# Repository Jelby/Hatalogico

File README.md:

##Hatalogico
Libraries for the Hatalogico Raspberry Pi Hat

###Cloning This Repo
When cloning, it is crucial that you use the --recursive switch in order to fetch the Adafruit submodules.

All the python files required to drive the I2C chips on the Hatalogico were written and are maintained by [Adafruit Industries](https://www.adafruit.com/). I have simply included them as submodules and written a few examples using them.

Before using these files, you need to setup your Pi for GPIO and I2C (note the Pi 2 has a slightly different method for the latter).

[Setting up the I2C](https://learn.adafruit.com/adafruits-raspberry-pi-lesson-4-gpio-setup/configuring-i2c)

[Setting up the GPIO](https://learn.adafruit.com/adafruits-raspberry-pi-lesson-4-gpio-setup/configuring-gpio)

##Installing
The RPi2 is slightly different but I recommend you 'apt-get' the following packages on both platforms:

**sudo apt-get update -y**  
**sudo apt-get install -y python-dev python-rpi.gpio python-smbus**  
**sudo apt-get install -y i2c-tools libi2c-dev**

You can copy and paste all 3 lines into your terminal and they will run one after the other (synchronously).

You will need to add the I2C tools to both versions:  
**sudo nano /etc/modules**

Scroll to the bottom and add:  
**i2c-dev**

####For RPi B+ and older only:
Also add a new line underneath 'i2c-dev':  
**i2c-bcm2708**

Crtl-X to close, pressing Y to save the changes (overwrite with the same name by pressing enter)

####For the RPi B+ or older you will need to update the blacklist file:  
**sudo nano /etc/modprobe.d/raspi-blacklist.conf**

Update it to read:  
\#blacklist spi-bcm2708  
\#blacklist i2c-bcm2708

After all of this, it's wise to do a little housekeeping (perhaps even removing some unused libraries):  
**sudo apt-get -y purge wolfram-engine**  
**sudo apt-get -y autoremove**  
**sudo apt-get -y clean**  
**sudo apt-get -y update**  
**sudo apt-get -y dist-upgrade**  

#I2C Addresses
(on the prototype model)

1. 16 Channel PWM: **0x70**
2. 4 Channel ADC #1: **0x49**
3. 4 Channel ADC #2: **0x48**
4. Single Channel DAC #1: **0x60**
5. Single Channel DAC #2: **0x61**

###Big thanks to Adafruit without whom the Hatalogico would just be a mug coaster.

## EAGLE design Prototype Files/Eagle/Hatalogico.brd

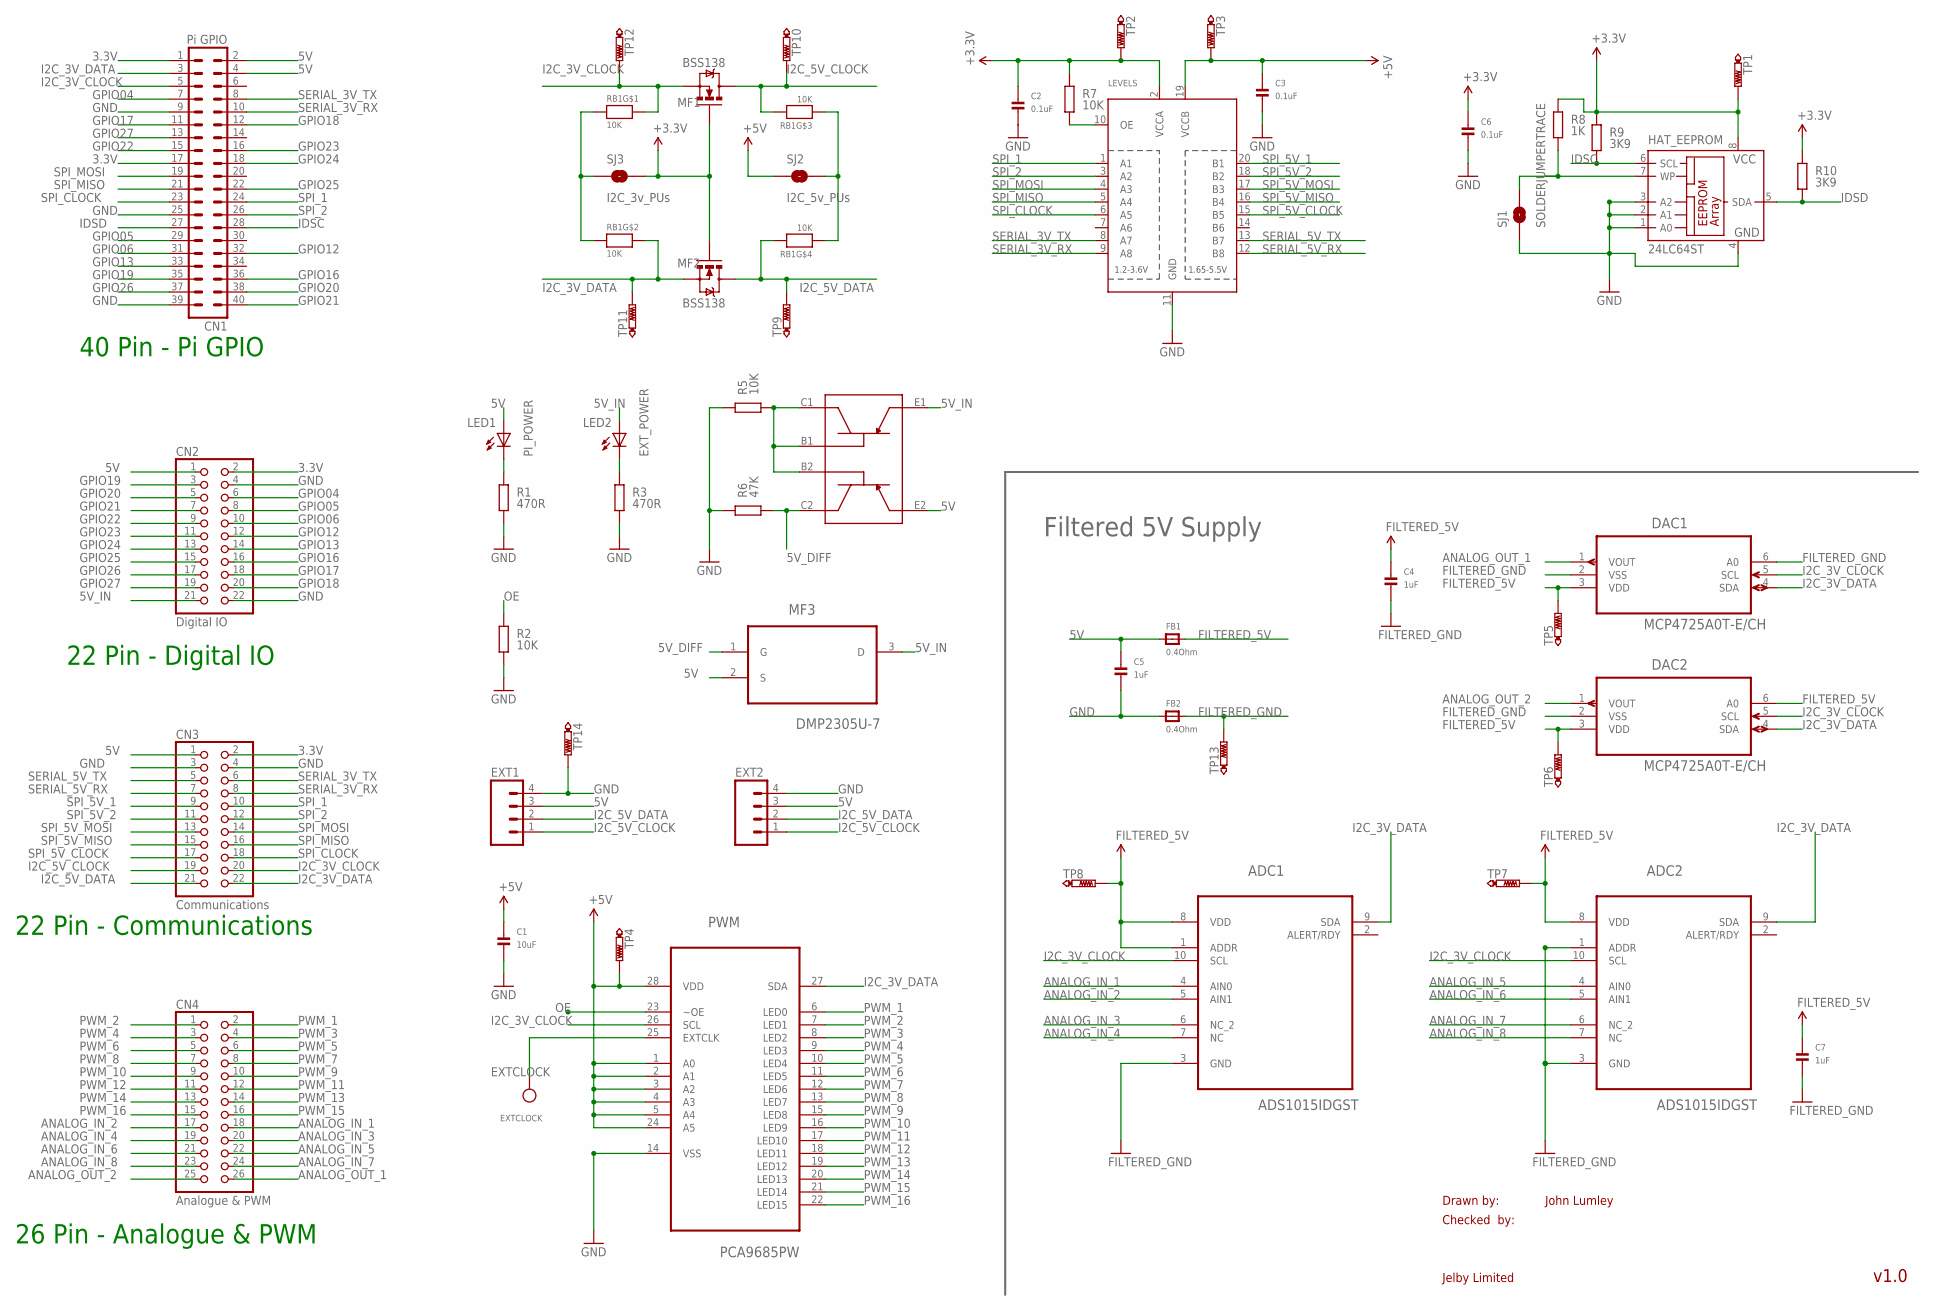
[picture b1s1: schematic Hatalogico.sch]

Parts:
ADC1, ADC2: ADS1015IDGST; SOP50P490X110-10N
C1: 10uF; 0603
C2, C3, C6: 0.1uF; 0603
C4, C5, C7: 1uF; 0603
CN1: Pi GPIO; PIN_20X2
CN2: Digital IO; 2X11
CN3: Communications; 2X11
CN4: Analogue & PWM; 2X13
DAC1, DAC2: MCP4725A0T-E/CH; SOT95P270X145-6N
EXT1, EXT2: 1X04_HEADER"; 1X04_HEADER
EXTCLOCK: TESTPOINT0.1"; 1X01_ROUND
FB1, FB2: 0.4Ohm; 0805
HAT_EEPROM: 24LC64ST; TSSOP8
LED1: PI_POWER; CHIPLED_1206
LED2: EXT_POWER; CHIPLED_1206
LEVELS: TXB0108PWR; TSSOP20
MF1, MF2: BSS138; SOT23-3
MF3: DMP2305U-7; SOT103P240X110-3N
PWM: PCA9685PW; SOP65P640X110-28N
R1, R3: 470R; M0805; TOLERANCE 5%
R2, R5, R7: 10K; M0805; TOLERANCE 5%
R6: 47K; M0805; TOLERANCE 5%
R8: 1K; M0805; TOLERANCE 5%
R9, R10: 3K9; M0805; TOLERANCE 5%
RB1: 10K; RESPACK_4X0603
SJ1: SOLDERJUMPERTRACE; SJ_2S-TRACE
SJ2: I2C_5v_PUs; PAD-JUMPER-2-NO_YES_SILK
SJ3: I2C_3v_PUs; PAD-JUMPER-2-NO_YES_SILK
T1: DMMT5401
TP1, TP2, TP3, TP4, TP5, TP6, TP7, TP8, TP9, TP10, TP11, TP12, TP13, TP14: PTR1TP20SQ; TP20SQ

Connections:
3.3V: C2.1, C6.1, CN1.1, CN1.17, CN2.2, CN3.2, HAT_EEPROM.8 (VCC), LEVELS.2 (VCCA), MF1.1 (G), MF2.1 (G), R7.2, R8.2, R9.2, R10.2, SJ3.2, TP1.TP, TP2.TP
5V: C1.1, C3.1, C5.1, CN1.2, CN1.4, CN2.1, CN3.1, EXT1.3, EXT2.3, FB1.1, LED1.A, LEVELS.19 (VCCB), MF3.2 (S), PWM.1 (A0), PWM.2 (A1), PWM.3 (A2), PWM.4 (A3), PWM.5 (A4), PWM.24 (A5), PWM.28 (VDD), SJ2.1, T1.E2, TP3.TP, TP4.TP
5V_DIFF: MF3.1 (G), R6.1, T1.C2
5V_IN: CN2.21, LED2.A, MF3.3 (D), T1.E1
ANALOG_IN_1: ADC1.4 (AIN0), CN4.18
ANALOG_IN_2: ADC1.5 (AIN1), CN4.17
ANALOG_IN_3: ADC1.6 (NC_2), CN4.20
ANALOG_IN_4: ADC1.7 (NC), CN4.19
ANALOG_IN_5: ADC2.4 (AIN0), CN4.22
ANALOG_IN_6: ADC2.5 (AIN1), CN4.21
ANALOG_IN_7: ADC2.6 (NC_2), CN4.24
ANALOG_IN_8: ADC2.7 (NC), CN4.23
ANALOG_OUT_1: CN4.26, DAC1.1 (VOUT)
ANALOG_OUT_2: CN4.25, DAC2.1 (VOUT)
EXTCLOCK: EXTCLOCK.1, PWM.25 (EXTCLK)
FILTERED_5V: ADC1.1 (ADDR), ADC1.8 (VDD), ADC2.8 (VDD), C4.1, C7.1, DAC1.3 (VDD), DAC2.3 (VDD), DAC2.6 (A0), FB1.2, TP5.TP, TP6.TP, TP7.TP, TP8.TP
FILTERED_GND: ADC1.3 (GND), ADC2.1 (ADDR), ADC2.3 (GND), C4.2, C7.2, DAC1.2 (VSS), DAC1.6 (A0), DAC2.2 (VSS), FB2.2, TP13.TP
GND: C1.2, C2.2, C3.2, C5.2, C6.2, CN1.9, CN1.25, CN1.39, CN2.4, CN2.22, CN3.3, CN3.4, EXT1.4, EXT2.4, FB2.1, HAT_EEPROM.1 (A0), HAT_EEPROM.2 (A1), HAT_EEPROM.3 (A2), HAT_EEPROM.4 (GND), LEVELS.11 (GND), PWM.14 (VSS), R1.1, R2.1, R3.1, R5.2, R6.2, SJ1.1, TP14.TP
GPIO04: CN1.7, CN2.6
GPIO05: CN1.29, CN2.8
GPIO06: CN1.31, CN2.10
GPIO12: CN1.32, CN2.12
GPIO13: CN1.33, CN2.14
GPIO16: CN1.36, CN2.16
GPIO17: CN1.11, CN2.18
GPIO18: CN1.12, CN2.20
GPIO19: CN1.35, CN2.3
GPIO20: CN1.38, CN2.5
GPIO21: CN1.40, CN2.7
GPIO22: CN1.15, CN2.9
GPIO23: CN1.16, CN2.11
GPIO24: CN1.18, CN2.13
GPIO25: CN1.22, CN2.15
GPIO26: CN1.37, CN2.17
GPIO27: CN1.13, CN2.19
I2C_3V_CLOCK: ADC1.10 (SCL), ADC2.10 (SCL), CN1.5, CN3.20, DAC1.5 (SCL), DAC2.5 (SCL), MF1.2 (S), PWM.26 (SCL), RB1.8 (2), TP12.TP
I2C_3V_DATA: ADC1.9 (SDA), ADC2.9 (SDA), CN1.3, CN3.22, DAC1.4 (SDA), DAC2.4 (SDA), MF2.2 (S), PWM.27 (SDA), RB1.7 (2), TP11.TP
I2C_5V_CLOCK: CN3.19, EXT1.1, EXT2.1, MF1.3 (D), RB1.6 (2), TP10.TP
I2C_5V_DATA: CN3.21, EXT1.2, EXT2.2, MF2.3 (D), RB1.5 (2), TP9.TP
IDSC: CN1.28, HAT_EEPROM.6 (SCL), R9.1
IDSD: CN1.27, HAT_EEPROM.5 (SDA), R10.1
LEDOUT: LED1.C, R1.2
LEDOUT1: LED2.C, R3.2
unnamed: R5.1, T1.B1, T1.B2, T1.C1
unnamed: RB1.1, RB1.2 (1), SJ3.1
unnamed: RB1.3 (1), RB1.4 (1), SJ2.2
unnamed: LEVELS.10 (OE), R7.1
OE: PWM.23 (~OE), R2.2
PWM_1: CN4.2, PWM.6 (LED0)
PWM_2: CN4.1, PWM.7 (LED1)
PWM_3: CN4.4, PWM.8 (LED2)
PWM_4: CN4.3, PWM.9 (LED3)
PWM_5: CN4.6, PWM.10 (LED4)
PWM_6: CN4.5, PWM.11 (LED5)
PWM_7: CN4.8, PWM.12 (LED6)
PWM_8: CN4.7, PWM.13 (LED7)
PWM_9: CN4.10, PWM.15 (LED8)
PWM_10: CN4.9, PWM.16 (LED9)
PWM_11: CN4.12, PWM.17 (LED10)
PWM_12: CN4.11, PWM.18 (LED11)
PWM_13: CN4.14, PWM.19 (LED12)
PWM_14: CN4.13, PWM.20 (LED13)
PWM_15: CN4.16, PWM.21 (LED14)
PWM_16: CN4.15, PWM.22 (LED15)
SERIAL_3V_RX: CN1.10, CN3.8, LEVELS.9 (A8)
SERIAL_3V_TX: CN1.8, CN3.6, LEVELS.8 (A7)
SERIAL_5V_RX: CN3.7, LEVELS.12 (B8)
SERIAL_5V_TX: CN3.5, LEVELS.13 (B7)
SPI_1: CN1.24, CN3.10, LEVELS.1 (A1)
SPI_2: CN1.26, CN3.12, LEVELS.3 (A2)
SPI_5V_1: CN3.9, LEVELS.20 (B1)
SPI_5V_2: CN3.11, LEVELS.18 (B2)
SPI_5V_CLOCK: CN3.17, LEVELS.15 (B5)
SPI_5V_MISO: CN3.15, LEVELS.16 (B4)
SPI_5V_MOSI: CN3.13, LEVELS.17 (B3)
SPI_CLOCK: CN1.23, CN3.18, LEVELS.6 (A5)
SPI_MISO: CN1.21, CN3.16, LEVELS.5 (A4)
SPI_MOSI: CN1.19, CN3.14, LEVELS.4 (A3)
WP: HAT_EEPROM.7 (WP), R8.1, SJ1.2

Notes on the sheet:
Drawn by:
Checked by:
Jelby Limited
John Lumley
v1.0
40 Pin - Pi GPIO
26 Pin - Analogue & PWM
22 Pin - Digital IO
22 Pin - Communications
Filtered 5V Supply

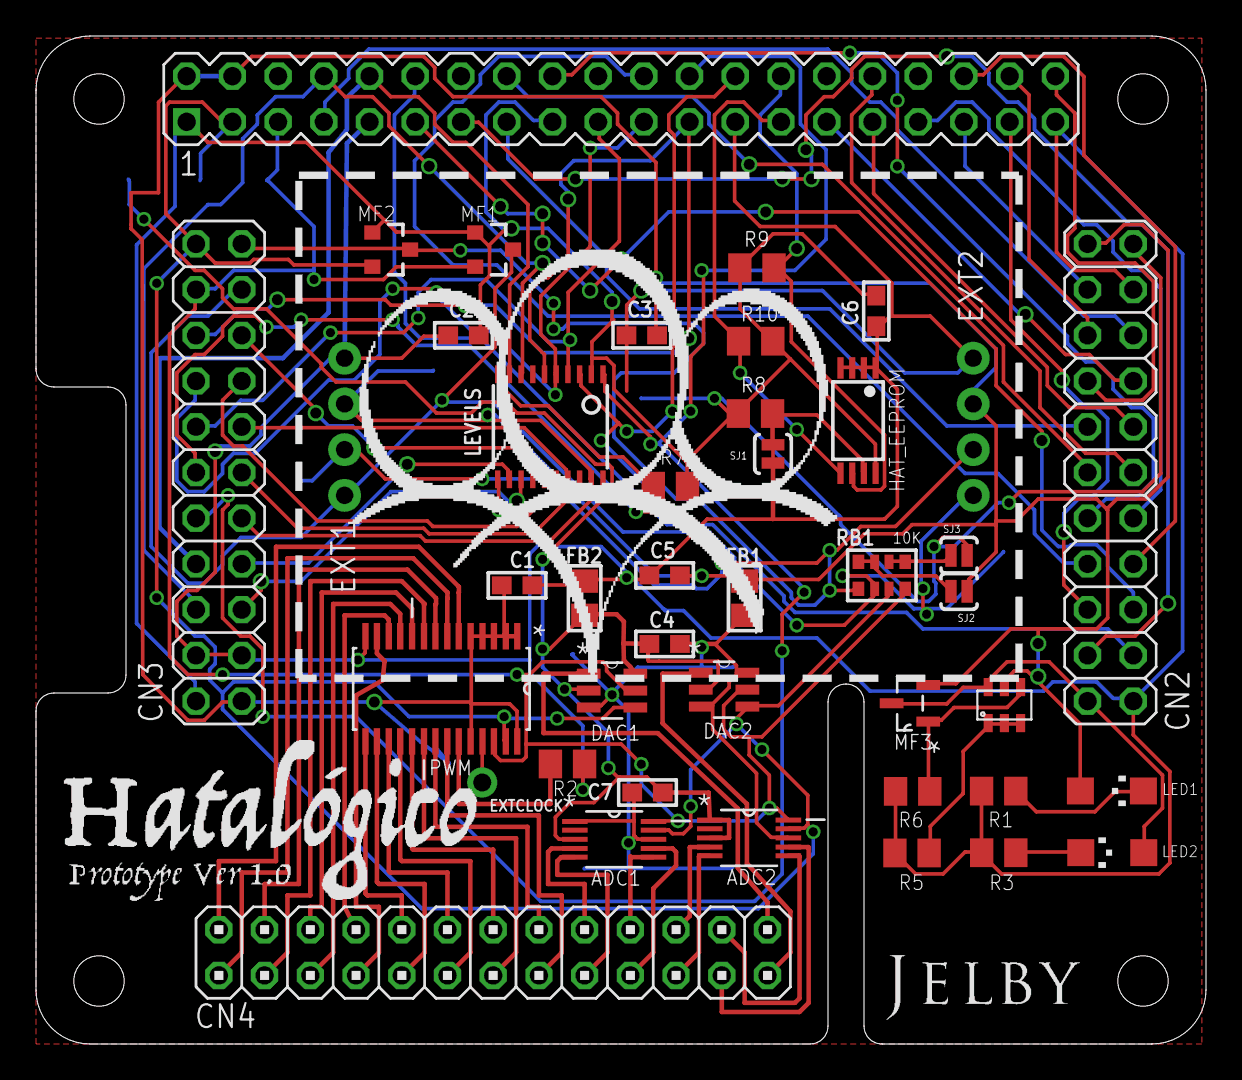
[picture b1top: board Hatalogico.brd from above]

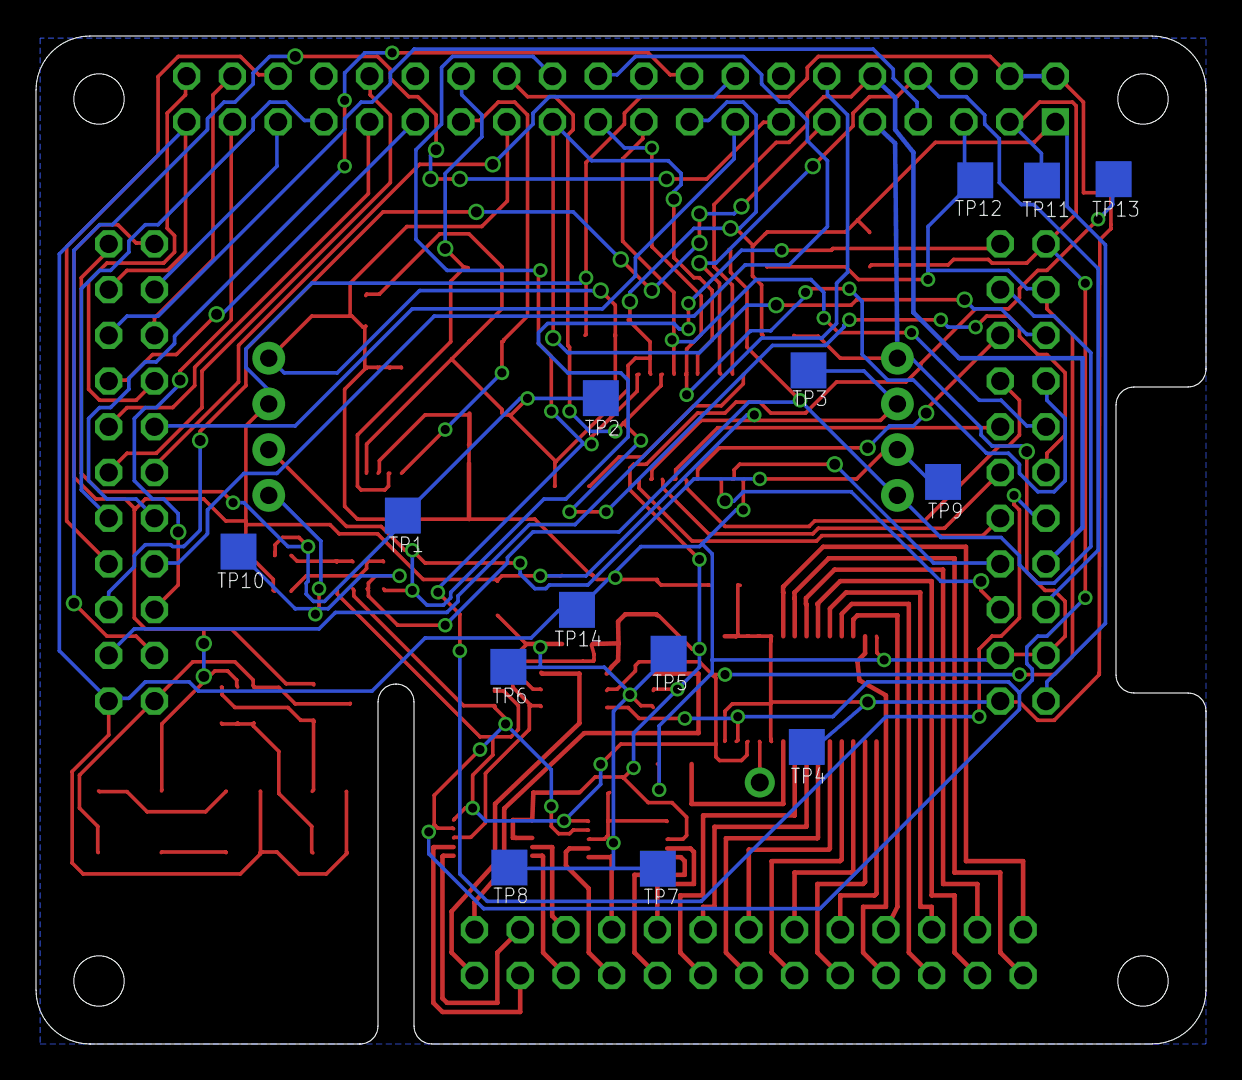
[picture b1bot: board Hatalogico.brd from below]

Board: 2 copper layers, 65.0 x 56.0 mm, 56 parts (14 on the bottom side), 79 nets.

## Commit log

2015-03-22 Initial README
2015-03-22 Adding first examples
    LED PWM example
    DAC to ADC example
2015-03-24 Updating LED examples
    And a startup test script
2015-03-24 Pulling Adafruit updates
2015-03-24 Adding I2C addesses
2015-03-24 Spacing tweaks
2015-03-24 Formatting tweaks
2015-03-24 Formatting
2015-03-27 Example updates
2015-03-28 Updates to examples
2015-03-29 Schematics and design files
2015-04-12 Random LED timing tweak
2015-04-12 Adding apt-get config
2015-04-12 Better EOLs
2015-04-12 Readme tweak
2015-04-13 Readme tweaks
2015-04-13 KnightRider example
2015-04-13 KR time tweak
2015-04-13 Reverse KR brightnesses for sinking not sourcing
2015-04-13 KR Time Tweaks
2015-04-13 Typo
2015-04-13 KR Tweaks
2015-04-13 KR Tweak
2015-04-13 Tweak
2015-04-13 Startup testing
2015-04-13 KR Testing
2015-04-13 Testing
2015-04-14 Tweaks
2015-04-16 Some more example tweaks
2015-05-01 H-Bridge tweak
2015-05-08 Added cloning advice

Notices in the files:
parts and their libraries:
microbuilder: This work is placed in the public domain, and may be freely used for commercial and non-commercial work with the following conditions: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
SparkFun-Passives: Licensing: Creative Commons ShareAlike 4.0 International - https://creativecommons.org/licenses/by-sa/4.0
